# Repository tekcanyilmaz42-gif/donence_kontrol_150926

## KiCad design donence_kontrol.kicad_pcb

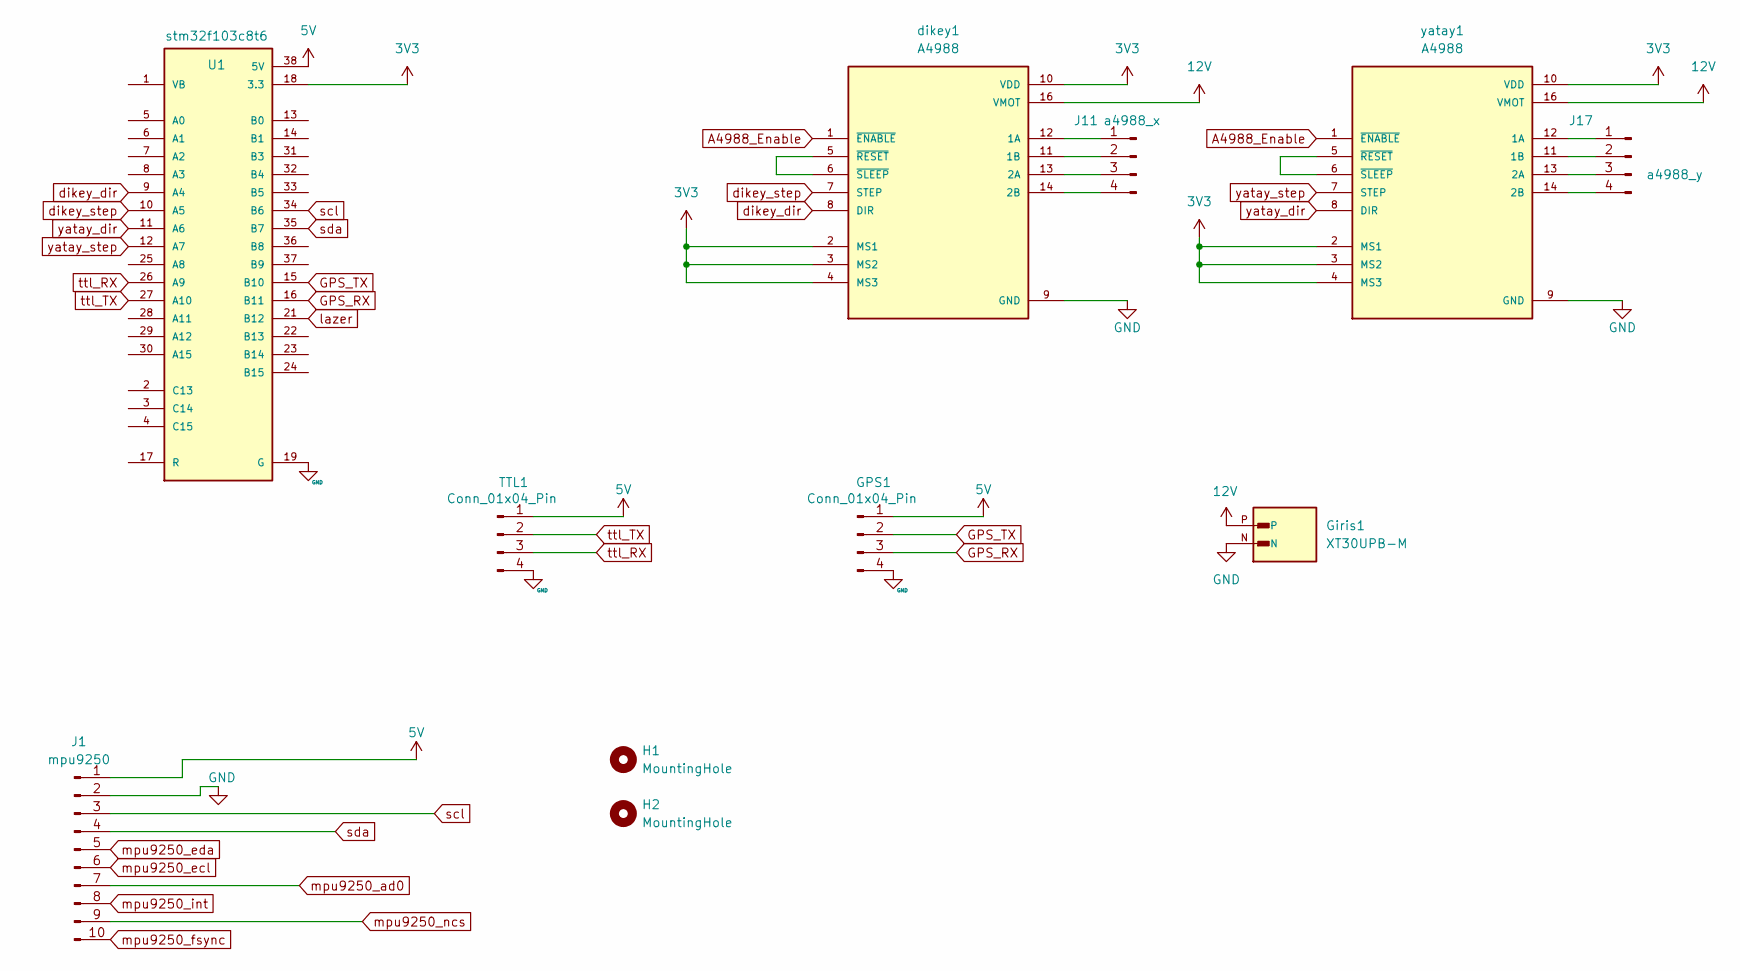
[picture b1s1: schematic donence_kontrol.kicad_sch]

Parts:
GPS1: Conn_01x04_Pin; PinHeader_1x04_P2.54mm_Vertical
Giris1: XT30UPB-M; AMASS_XT30UPB-M
H1, H2: MountingHole; MountingHole_2.2mm_M2_ISO7380_Pad
J1: mpu9250; PinHeader_1x10_P2.54mm_Vertical
J11: a4988_x; PinHeader_1x04_P2.54mm_Vertical
J17: a4988_y; PinHeader_1x04_P2.54mm_Vertical
TTL1: Conn_01x04_Pin; PinHeader_1x04_P2.54mm_Vertical
U1: stm32f103c8t6
dikey1: A4988; MODULE_A4988_STEPPER_MOTOR_DRIVER_CARRIER
yatay1: A4988; MODULE_A4988_STEPPER_MOTOR_DRIVER_CARRIER

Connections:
3V3: U1.18 (3.3), U1.40 (3.3), dikey1.2 (MS1), dikey1.3 (MS2), dikey1.4 (MS3), dikey1.10 (VDD), yatay1.2 (MS1), yatay1.3 (MS2), yatay1.4 (MS3), yatay1.10 (VDD)
5V: GPS1.1, J1.1, TTL1.1, U1.38 (5V)
12V: Giris1.P, dikey1.16 (VMOT), yatay1.16 (VMOT)
A4988_Enable: dikey1.1 (~ENABLE), yatay1.1 (~ENABLE)
GND: GPS1.4, Giris1.N, J1.2, TTL1.4, U1.19 (G), U1.20 (G), U1.39 (G), dikey1.9 (GND), dikey1.15 (GND), yatay1.9 (GND), yatay1.15 (GND)
GPS_RX: GPS1.3, U1.16 (B11)
GPS_TX: GPS1.2, U1.15 (B10)
unnamed: J11.1, dikey1.12 (1A)
unnamed: J11.2, dikey1.11 (1B)
unnamed: J11.3, dikey1.13 (2A)
unnamed: J11.4, dikey1.14 (2B)
unnamed: J17.1, yatay1.12 (1A)
unnamed: J17.2, yatay1.11 (1B)
unnamed: J17.3, yatay1.13 (2A)
unnamed: J17.4, yatay1.14 (2B)
unnamed: dikey1.5 (~RESET), dikey1.6 (~SLEEP)
unnamed: yatay1.5 (~RESET), yatay1.6 (~SLEEP)
dikey_dir: U1.9 (A4), dikey1.8 (DIR)
dikey_step: U1.10 (A5), dikey1.7 (STEP)
mpu9250_ad0: J1.7
mpu9250_ecl: J1.6
mpu9250_eda: J1.5
mpu9250_fsync: J1.10
mpu9250_int: J1.8
mpu9250_ncs: J1.9
scl: J1.3, U1.34 (B6)
sda: J1.4, U1.35 (B7)
ttl_RX: TTL1.3, U1.26 (A9)
ttl_TX: TTL1.2, U1.27 (A10)
yatay_dir: U1.11 (A6), yatay1.8 (DIR)
yatay_step: U1.12 (A7), yatay1.7 (STEP)

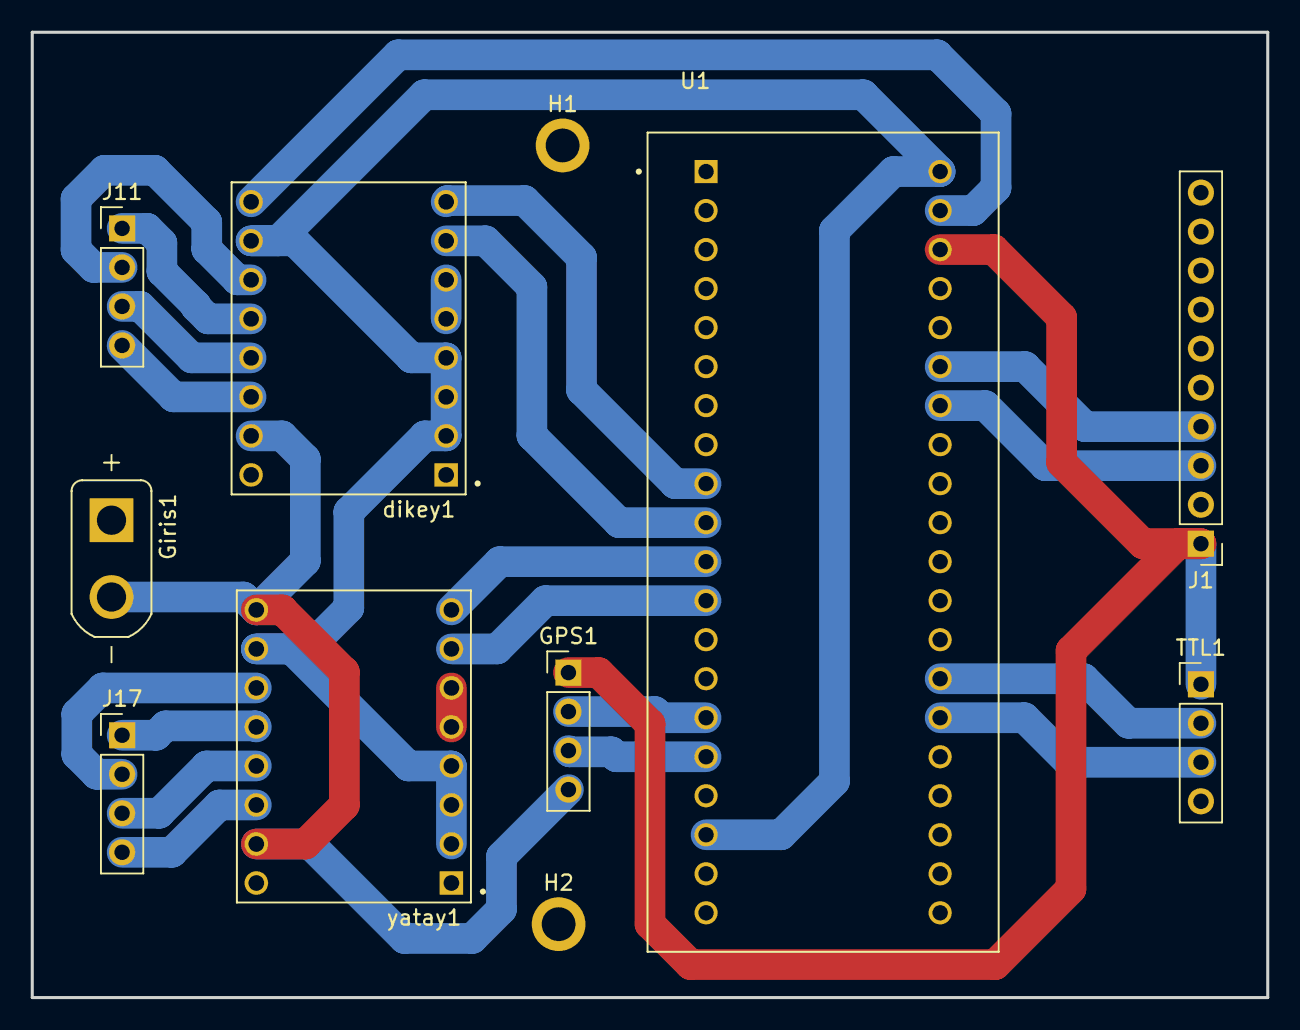
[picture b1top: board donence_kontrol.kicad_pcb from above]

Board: 2 copper layers, 80.4 x 62.9 mm, 11 parts (0 on the bottom side), 25 nets.
